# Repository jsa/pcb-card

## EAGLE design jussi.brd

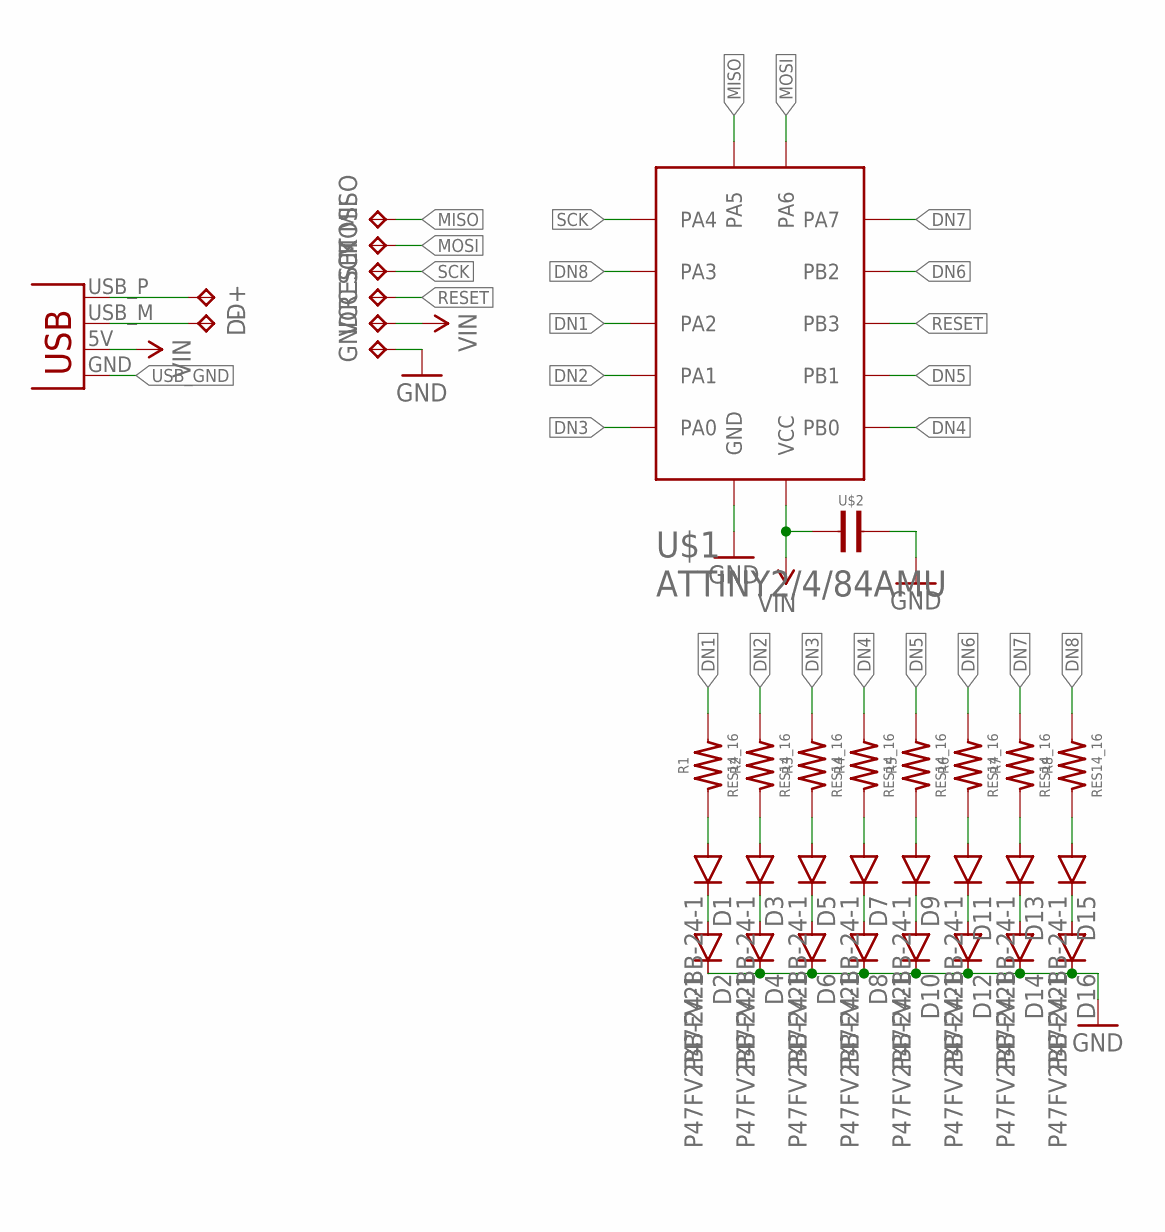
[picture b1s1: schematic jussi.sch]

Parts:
D1, D2, D3, D4, D5, D6, D7, D8, D9, D10, D11, D12, D13, D14, D15, D16: P47FV2BB-24-1; P47F
D+: TPTP08R; TP08R
D-: TPTP08R; TP08R
GND: TPTP08R; TP08R
JP1: USBPCB; USB-A-PCB
MISO: TPTP08R; TP08R
MOSI: TPTP08R; TP08R
R1, R2, R3, R4, R5, R6, R7, R8: RES14_16; 0402
RESET: TPTP08R; TP08R
SCK: TPTP08R; TP08R
U$1: ATTINY2/4/84AMU; 20-WFQFN
U$2: CAP47UF_10V; 0805
VCC: TPTP08R; TP08R

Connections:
D+: D+.TP, JP1.USB_P (D+)
D-: D-.TP, JP1.USB_M (D-)
DN1: R1.2, U$1.3 (PA2)
DN2: R2.2, U$1.4 (PA1)
DN3: R3.2, U$1.5 (PA0)
DN4: R4.2, U$1.11 (PB0)
DN5: R5.2, U$1.12 (PB1)
DN6: R6.2, U$1.14 (PB2)
DN7: R7.2, U$1.15 (PA7)
DN8: R8.2, U$1.2 (PA3)
GND: D2.C, D4.C, D6.C, D8.C, D10.C, D12.C, D14.C, D16.C, GND.TP, U$1.8 (GND), U$1.PAD (GND), U$2.2
MISO: MISO.TP, U$1.20 (PA5)
MOSI: MOSI.TP, U$1.16 (PA6)
unnamed: D1.C, D2.A
unnamed: D3.C, D4.A
unnamed: D5.C, D6.A
unnamed: D7.C, D8.A
unnamed: D9.C, D10.A
unnamed: D11.C, D12.A
unnamed: D13.C, D14.A
unnamed: D15.C, D16.A
unnamed: D1.A, R1.1
unnamed: D3.A, R2.1
unnamed: D5.A, R3.1
unnamed: D7.A, R4.1
unnamed: D9.A, R5.1
unnamed: D11.A, R6.1
unnamed: D13.A, R7.1
unnamed: D15.A, R8.1
RESET: RESET.TP, U$1.13 (PB3)
SCK: SCK.TP, U$1.1 (PA4)
USB_GND: JP1.GND
VIN: JP1.5V (VBUS), U$1.9 (VCC), U$2.1, VCC.TP

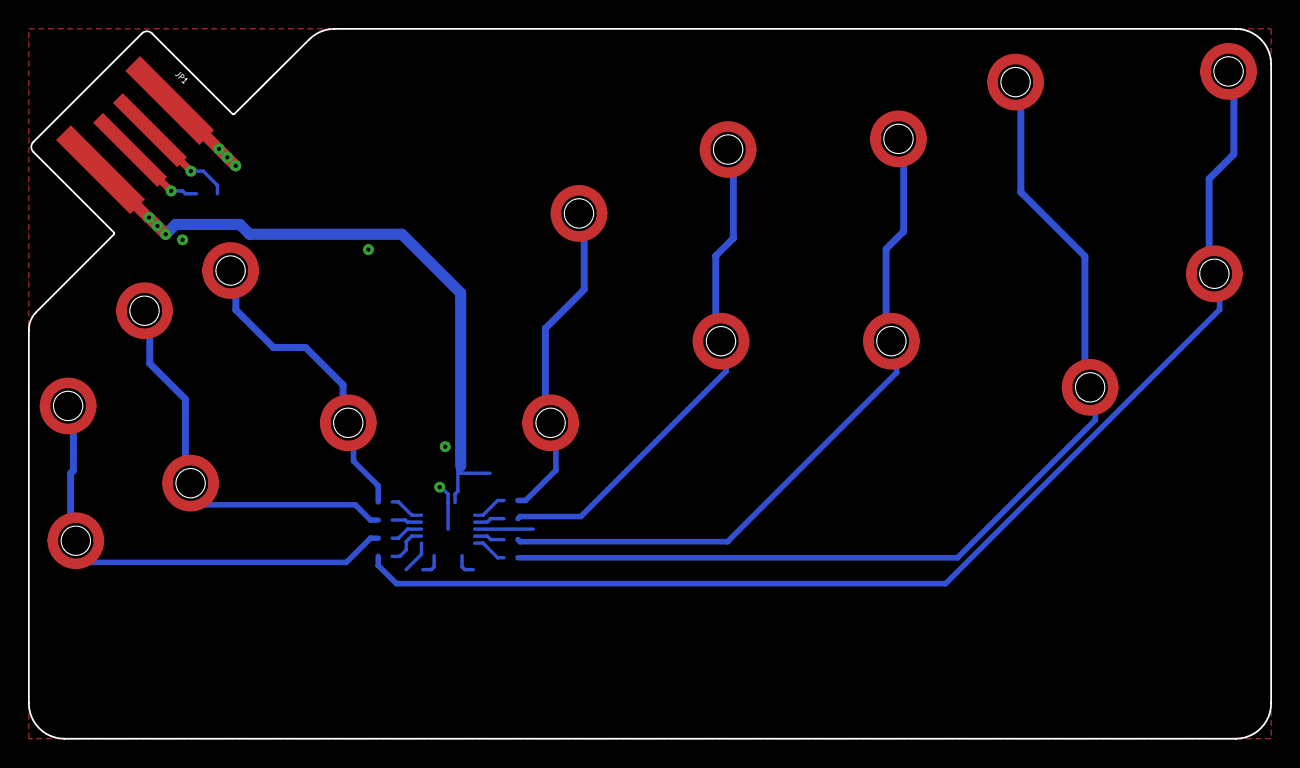
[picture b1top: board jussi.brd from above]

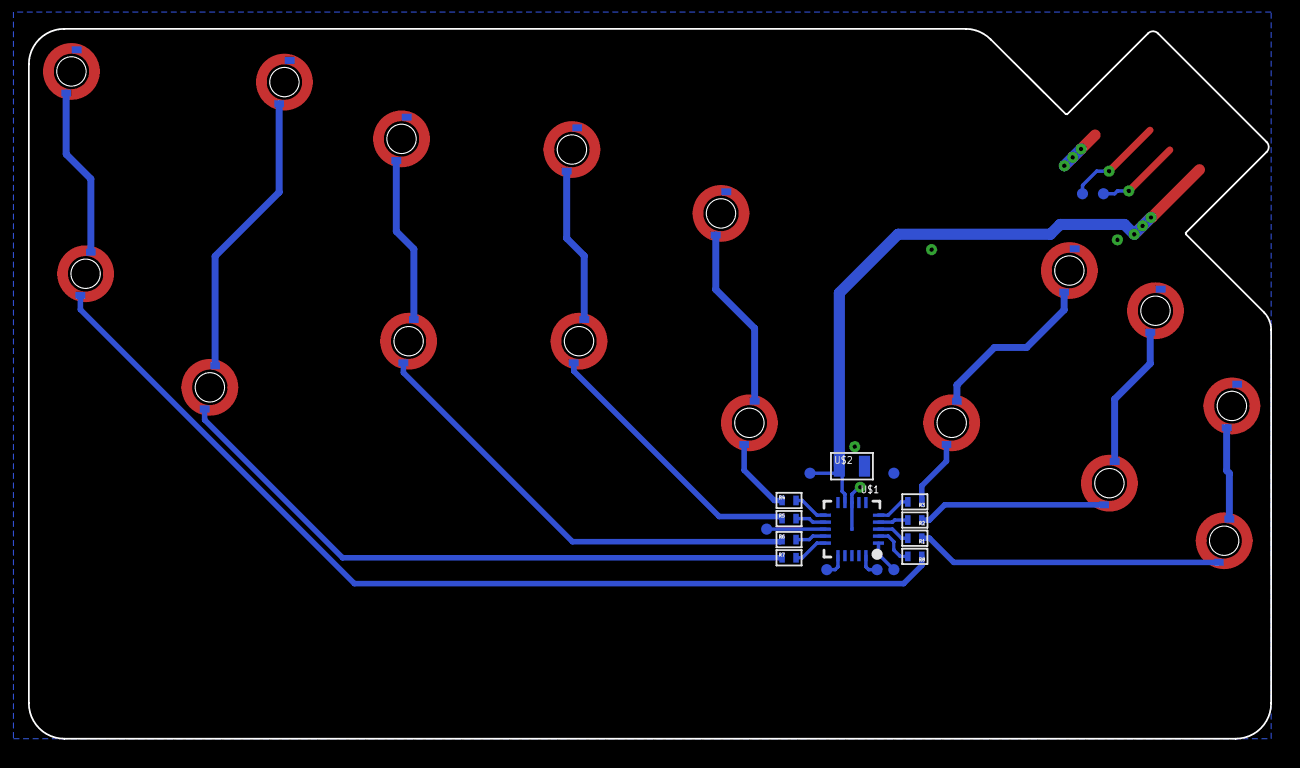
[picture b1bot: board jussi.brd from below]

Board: 2 copper layers, 88.9 x 50.8 mm, 35 parts (18 on the bottom side), 32 nets.

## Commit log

2015-12-25 Layers
2015-12-25 Both logo texts
2015-12-25 pre-merge
2015-12-26 Draft final
2015-12-26 PCB drafting
2015-12-26 "Done"
2015-12-26 Copper closer to holes
2015-12-27 Zip generated
2015-12-30 Some tweaks
2015-12-30 Moving LEDs

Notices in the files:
parts and their libraries:
SparkFun-Connectors: Licensing: Creative Commons ShareAlike 4.0 International - https://creativecommons.org/licenses/by-sa/4.0
